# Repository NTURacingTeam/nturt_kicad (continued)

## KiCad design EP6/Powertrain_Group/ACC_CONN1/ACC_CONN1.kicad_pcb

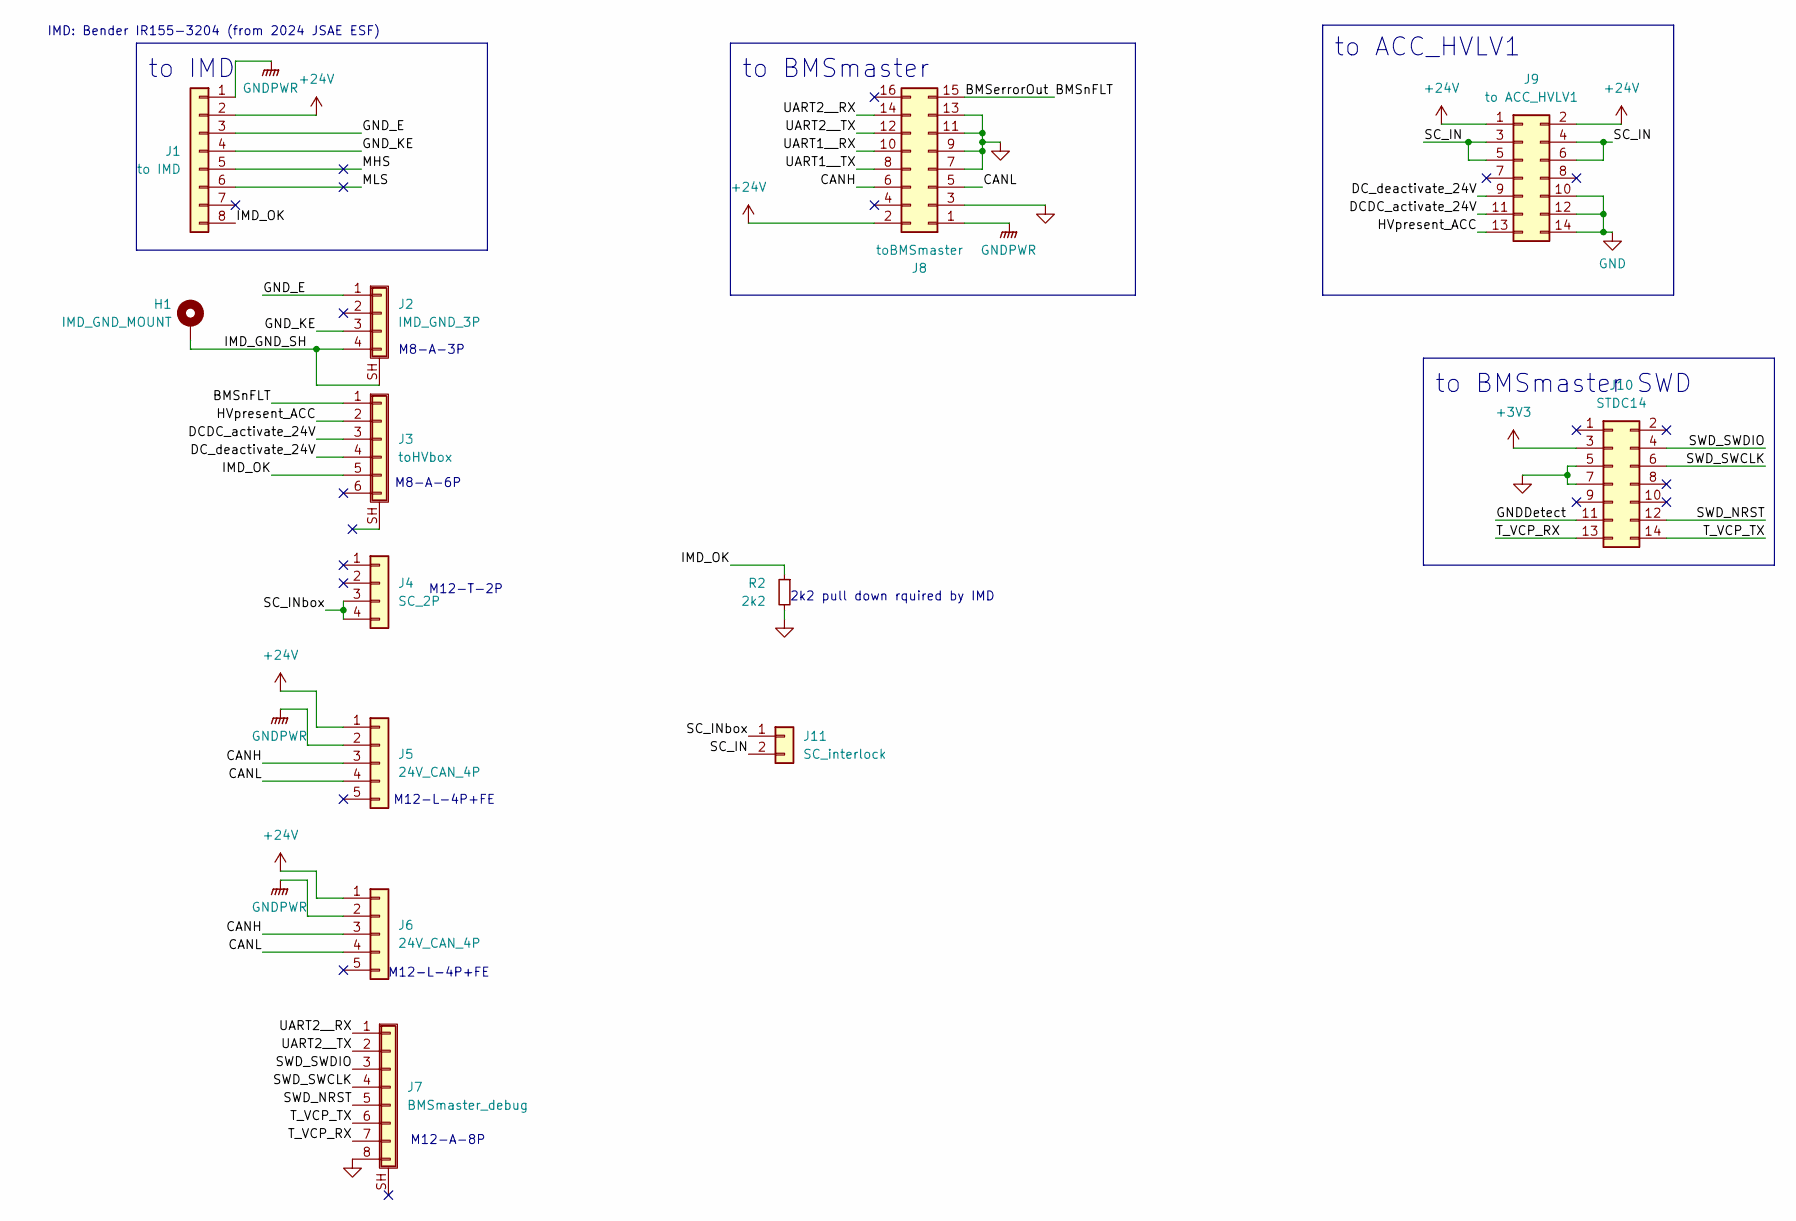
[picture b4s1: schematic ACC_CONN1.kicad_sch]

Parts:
H1: IMD_GND_MOUNT; MountingHole_3.2mm_M3_Pad_Via
J1: to IMD; JST_XH_B8B-XH-A_1x08_P2.50mm_Vertical
J2: IMD_GND_3P; WP-03F3-09-11
J3: toHVbox; WP-06F3-09-11
J4: SC_2P; NianYeong-M12-T-M4P
J5, J6: 24V_CAN_4P; NianYeong-M12-L-F5P
J7: BMSmaster_debug; NianYeong-M12-A-F8P-Shield
J8: toBMSmaster; IDC-Header_2x08_P2.54mm_Horizontal
J9: to ACC_HVLV1; IDC-Header_2x07_P2.54mm_Vertical
J10: STDC14; box_header_14P_pitch127
J11: SC_interlock; JST_VH_B2P-VH_1x02_P3.96mm_Vertical
R2: 2k2; R_0805_2012Metric

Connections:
+3V3: J10.3
+24V: J1.2, J5.1, J6.1, J8.2, J9.1, J9.2
/BMSerrorOut: J3.1, J8.15
/CANH: J5.3, J6.3, J8.6
/CANL: J5.4, J6.4, J8.5
/DCDC_activate_24V: J3.3, J9.11
/DC_deactivate_24V: J3.4, J9.9
/GNDDetect: J10.11
/GND_E: J1.3, J2.1
/GND_KE: J1.4, J2.3
/HVpresent_ACC: J3.2, J9.13
/IMD_GND_SH: H1.1, J2.4, J2.SH (Shield)
/IMD_OK: J1.8, J3.5, R2.1
/MHS: J1.5
/MLS: J1.6
/SC_IN: J9.3, J9.4, J9.5, J9.6, J11.2
/SC_INbox: J4.3, J4.4, J11.1
/SWD_NRST: J7.5, J10.12
/SWD_SWCLK: J7.4, J10.6
/SWD_SWDIO: J7.3, J10.4
/T_VCP_RX: J7.7, J10.13
/T_VCP_TX: J7.6, J10.14
/UART1__RX: J8.10
/UART1__TX: J8.8
/UART2__RX: J7.1, J8.14
/UART2__TX: J7.2, J8.12
GND: J7.8, J8.3, J8.7, J8.9, J8.11, J8.13, J9.10, J9.12, J9.14, J10.5, J10.7, R2.2
GNDPWR: J1.1, J5.2, J6.2, J8.1

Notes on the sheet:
M12-T-2P
to BMSmaster SWD
M12-L-4P+FE
to BMSmaster
to IMD
to ACC_HVLV1
M8-A-6P
M8-A-3P
2k2 pull down rquired by IMD
IMD: Bender IR155-3204 (from 2024 JSAE ESF)
M12-A-8P

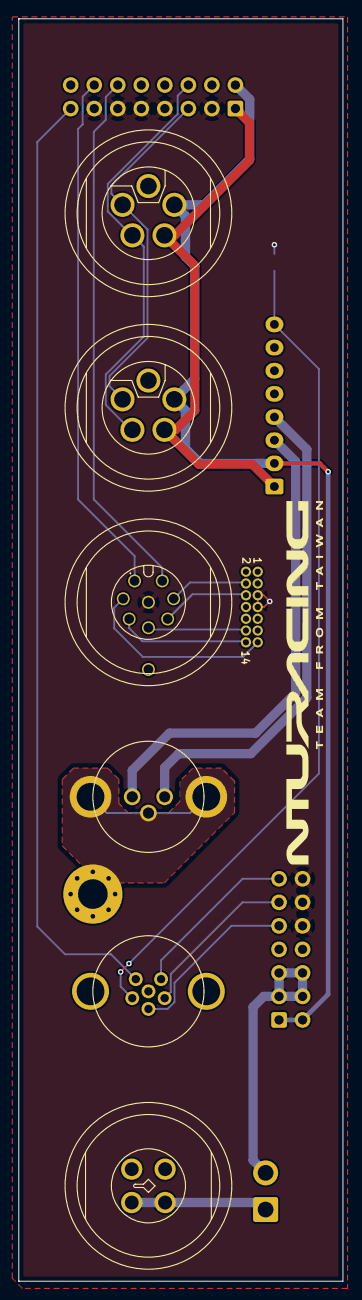
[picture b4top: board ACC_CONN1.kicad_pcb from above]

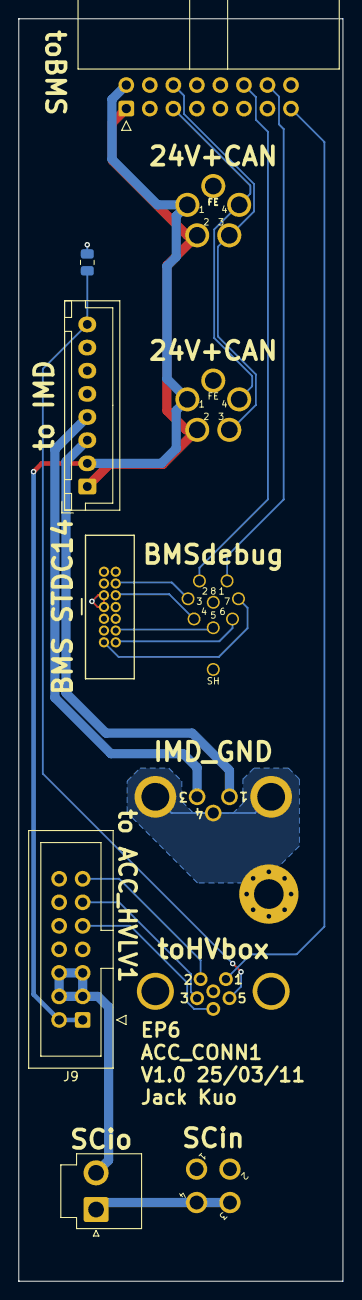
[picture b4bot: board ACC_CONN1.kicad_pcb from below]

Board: 2 copper layers, 35.0 x 136.3 mm, 13 parts (6 on the bottom side), 22 nets.

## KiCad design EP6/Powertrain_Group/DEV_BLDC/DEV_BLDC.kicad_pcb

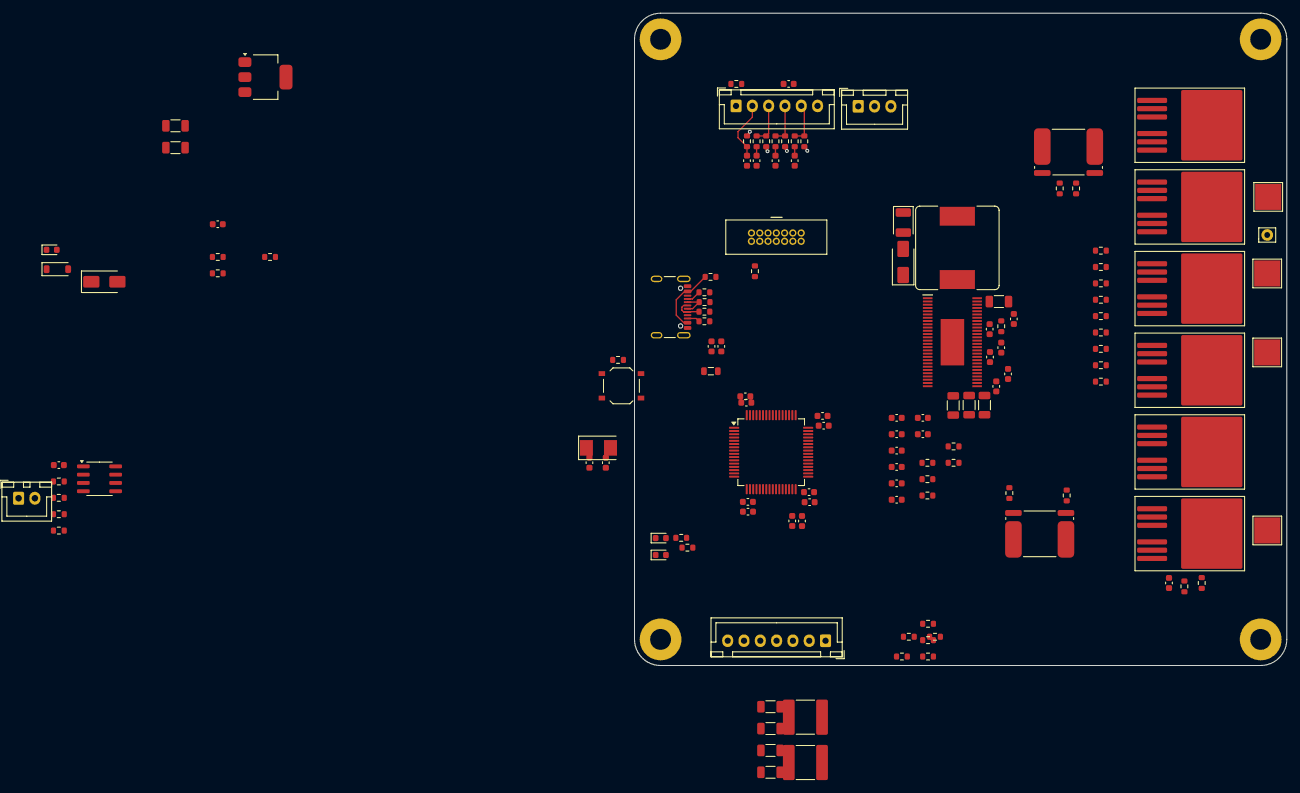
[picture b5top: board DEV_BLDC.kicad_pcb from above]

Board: 4 copper layers, 100.0 x 100.0 mm, 137 parts (0 on the bottom side), 92 nets.

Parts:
C1, C2: 33p; C_0603_1608Metric
C3, C4, C5, C6, C13: 10u 6V; C_0603_1608Metric
C7, C8, C9, C10, C14, C16: 0u1; C_0603_1608Metric
C11, C12, C21, C25, C26, C27, C28, C34: 2u2; C_0603_1608Metric
C15, C22, C39: 100n; C_0603_1608Metric
C17, C18, C19, C20: 4n7; C_0603_1608Metric
C23: 120p; C_0603_1608Metric
C24: 22n; C_0603_1608Metric
C29, C30, C36, C37, C47, C48, C49, C50: 10u 50V; C_1206_3216Metric
C31, C32: 47u 10V; C_1206_3216Metric
C33: 6n8; C_0603_1608Metric
C35, C38: 15u100V; C_2220_5750Metric
C40, C42, C43: 220n; C_0603_1608Metric
C44, C45: 2n2; C_0603_1608Metric
C46: 100u; CP_EIA-3528-12_Kemet-T
D1, D3: RED LED; LED_0603_1608Metric
D2: EMERALD LED; LED_0603_1608Metric
D4: 5.6V 1SMA5919A; D_SMA
D5: 3.3V 123 (BZT52B3V3); D_SOD-123
D7: SS54; D_SMA
FB1: GZ2012D601TF; L_0805_2012Metric
H1, H2, H3, H4: MountingHole_Pad; MountingHole_3.2mm_M3_Pad
IC1: DRV8302DCA; SOP50P810X120-57N
J1: STDC14; box_header_14P_pitch127
J2: USB_C_stm32; USB_C_Receptacle_GCT_USB4105-xx-A_16P_TopMnt_Horizontal
J3: CAN; JST_XH_B2B-XH-A_1x02_P2.50mm_Vertical
J4: HALL/Encoder; JST_XH_B6B-XH-A_1x06_P2.50mm_Vertical
J5: PWR_COMM; JST_XH_B7B-XH-A_1x07_P2.50mm_Vertical
J6: SERVER; JST_XH_B3B-XH-A_1x03_P2.50mm_Vertical
L2: 22uH ?A (); L_Bourns_SRR1260
Q1, Q2, Q3, Q4, Q5, Q6: IRFS7530-7P; TO-263-6
R1, R39, R40, R41, R42: 100R; R_0603_1608Metric
R2, R18, R23, R27: 10k; R_0603_1608Metric
R4, R30, R35, R37, R43, R49, R52: 39k; R_0603_1608Metric
R5, R15, R16, R17, R19, R20, R21, R31, R36, R38: 2k2; R_0603_1608Metric
R6, R7: 5k1; R_0603_1608Metric
R8, R9, R26: 10R; R_0603_1608Metric
R10, R12, R13, R14: 0R; R_0603_1608Metric
R11: 120R; R_0603_1608Metric
R22: NTC10k; R_0603_1608Metric
R24, R25, R32: 1k; R_0603_1608Metric
R28: 18k; R_0603_1608Metric
R29: 220k; R_0603_1608Metric
R33: 15k; R_0603_1608Metric
R34: 3k3; R_0603_1608Metric
R44: 1M; R_0603_1608Metric
R45, R46, R47, R48, R50, R51: 4R7; R_0603_1608Metric
R53, R54: SHUNT; R_Shunt_Isabellenhuette_BVR4026
SW1: TS-1187A-B-A-B; SW_Push_1P1T_XKB_TS-1187A
TP1: power+; Pin_D0.9mm_L10.0mm_W2.4mm_FlatFork
TP2: power-; TestPoint_Pad_4.0x4.0mm
TP3: P1; TestPoint_Pad_4.0x4.0mm
TP4: P2; TestPoint_Pad_4.0x4.0mm
TP5: P3; TestPoint_Pad_4.0x4.0mm
U1: STM32F405RGT6; LQFP-64_10x10mm_P0.5mm
U2: TJA1051T-3; SOIC-8_3.9x4.9mm_P1.27mm
U3: AMS1117-3.3; SOT-223-3_TabPin2
Y1: 8MHz X50328MSB2GI; Crystal_SMD_5032-2Pin_5.0x3.2mm

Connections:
+3V3: C3.1, C4.1, C5.1, C6.1, C7.1, C8.1, C9.1, C10.1, C16.1, C32.1, D5.1 (K), FB1.1, IC1.9 (M_OC), IC1.24 (REF), J1.3, J5.6, R15.1, R16.1, R17.1, R18.1, R22.1, R32.1, U1.1 (VBAT), U1.19 (VDD), U1.32 (VDD), U1.48 (VDD), U1.64 (VDD), U2.5 (VIO), U3.2 (VO)
+5V: C31.1, C46.1, D4.1 (K), J4.6, J5.7, J6.2, L2.2, R10.1, R28.1, U2.3 (VCC), U3.3 (VI)
/CAN/CANH: J3.2, R11.1, U2.7 (CANH)
/CAN/CANL: J3.1, R11.2, U2.6 (CANL)
/CAN/CAN_RX: R14.2, U1.61 (PB8)
/CAN/CAN_TX: R13.2, U1.62 (PB9)
/Filters/HALL1_IN: J4.5, R17.2, R21.1
/Filters/HALL1_OUT: C20.1, R21.2, U1.52 (PC11)
/Filters/HALL2_IN: J4.4, R16.2, R20.1
/Filters/HALL2_OUT: C19.1, R20.2, U1.59 (PB7)
/Filters/HALL3_IN: J4.3, R15.2, R19.1
/Filters/HALL3_OUT: C18.1, R19.2, U1.58 (PB6)
/Filters/TEMP_IN: C17.1, J4.2, R18.2, U1.8 (PC0)
/MCU/3V3_REF: C13.1, C14.1, FB1.2, U1.13 (VDDA)
/MCU/ADC_TEMP: C21.1, R22.2, R23.1, U1.17 (PA3)
/MCU/AN_IN: C15.1, R4.2, R5.1, U1.10 (PC2)
/MCU/BR_SO1: IC1.25 (SO1), U1.27 (PB1)
/MCU/BR_SO2: IC1.26 (SO2), U1.26 (PB0)
/MCU/DC_CAL: IC1.12 (DC_CAL), U1.33 (PB12)
/MCU/EN_GATE: IC1.16 (EN_GATE), U1.51 (PC10)
/MCU/FAULT: IC1.6 (NFAULT), U1.53 (PC12)
/MCU/H1: IC1.17 (INH_A), U1.43 (PA10)
/MCU/H2: IC1.19 (INH_B), U1.42 (PA9)
/MCU/H3: IC1.21 (INH_C), U1.41 (PA8)
/MCU/L1: IC1.18 (INL_A), U1.36 (PB15)
/MCU/L2: IC1.20 (INL_B), U1.35 (PB14)
/MCU/L3: IC1.22 (INL_C), U1.34 (PB13)
/MCU/LED_GREEN: R25.1, U1.24 (PC4)
/MCU/LED_RED: R24.1, U1.25 (PC5)
/MCU/MISO_ADC_EXT2: J5.2, U1.22 (PA6)
/MCU/NRST: J1.12, R1.2, U1.7 (NRST)
/MCU/OSC_IN: C1.1, U1.5 (PH0), Y1.1
/MCU/OSC_OUT: C2.1, U1.6 (PH1), Y1.2
/MCU/RESET: R1.1, SW1.2
/MCU/RX_SCL_MOSI: J5.3, U1.23 (PA7), U1.29 (PB10), U1.38 (PC7)
/MCU/SCK_ADC_EXT: J5.5, U1.21 (PA5)
/MCU/SENS1: R30.2, R31.1, U1.16 (PA2)
/MCU/SENS2: R35.2, R36.1, U1.15 (PA1)
/MCU/SENS3: R37.2, R38.1, U1.14 (PA0)
/MCU/SERVO: C22.1, R26.2, U1.57 (PB5)
/MCU/SWCLK: J1.6, U1.49 (PA14)
/MCU/SWDIO: J1.4, U1.46 (PA13)
/MCU/TX_SDA_NSS: J5.4, U1.20 (PA4), U1.30 (PB11), U1.37 (PC6)
/MCU/USB_DM: R8.1, U1.44 (PA11)
/MCU/USB_DP: R9.1, U1.45 (PA12)
/MOSFETdriver/H1_LOW: IC1.44 (SL_A), Q2.2 (S), Q2.3 (S), Q2.5 (S), Q2.6 (S), Q2.7 (S), R43.2, R54.1
/MOSFETdriver/H1_VS: C40.2, IC1.46 (SH_A), Q1.2 (S), Q1.3 (S), Q1.5 (S), Q1.6 (S), Q1.7 (S), Q2.4 (D), R37.1, TP3.1
/MOSFETdriver/H2_VS: C42.2, IC1.41 (SH_B), Q3.2 (S), Q4.4 (D), R35.1, TP4.1
/MOSFETdriver/H3_LOW: IC1.34 (SL_C), Q6.2 (S), Q6.3 (S), Q6.5 (S), Q6.6 (S), Q6.7 (S), R52.2, R53.1
/MOSFETdriver/H3_VS: C43.2, IC1.36 (SH_C), Q5.2 (S), Q6.4 (D), R30.1, TP5.1
/MOSFETdriver/M_H1: IC1.47 (GH_A), R45.1
/MOSFETdriver/M_H2: IC1.42 (GH_B), R47.1
/MOSFETdriver/M_H3: IC1.37 (GH_C), R50.1
/MOSFETdriver/M_L1: IC1.45 (GL_A), R46.1
/MOSFETdriver/M_L2: IC1.40 (GL_B), R48.1
/MOSFETdriver/M_L3: IC1.35 (GL_C), R51.1
/MOSFETdriver/SH1_A: R39.2, R53.2
/MOSFETdriver/SH1_B: R40.2, R53.3
/MOSFETdriver/SH2_A: R41.2, R54.2
/MOSFETdriver/SH2_B: R42.2, R54.3
/USB_D+: J2.A6 (D+), J2.B6 (D+), R9.2
/USB_D-: J2.A7 (D-), J2.B7 (D-), R8.2
GND: C1.2, C2.2, C3.2, C4.2, C5.2, C6.2, C7.2, C8.2, C9.2, C10.2, C11.2, C12.2, C13.2, C14.2, C15.2, C16.2, C17.2, C18.2, C19.2, C20.2, C21.2, C22.2, C23.2, C25.1, C26.1, C27.1, C28.1, C29.2, C30.2, C31.2, C32.2, C34.1, C35.2, C36.2, C37.2, C38.2, C46.2, C47.2, C48.2, C49.2, C50.2, D1.1 (K), D2.1 (K), D3.1 (K), D4.2 (A), D5.2 (A), D7.2 (A), IC1.8 (M_PWM), IC1.10 (GAIN), IC1.28 (AGND), IC1.39 (SL_B), IC1.57 (GND), J1.5, J1.7, J2.A1 (GND), J2.A12 (GND), J2.B1 (GND), J2.B12 (GND), J4.1, J5.1, J6.3, Q4.2 (S), Q4.3 (S), Q4.5 (S), Q4.6 (S), Q4.7 (S), R2.2, R5.2, R6.1, R7.1, R12.2, R23.2, R27.1, R29.2, R31.2, R33.2, R34.2, R36.2, R38.2, R44.2, R49.2, R53.4, R54.4, SW1.1, TP2.1, U1.12 (VSSA), U1.18 (VSS), U1.63 (VSS), U2.2 (GND), U3.1 (GND)
unnamed: C25.2, C26.2, IC1.13 (GVDD)
unnamed: C27.2, C34.2, IC1.11 (OC_ADJ), IC1.23 (DVDD)
unnamed: C39.2, D7.1 (K), IC1.50 (PH_1), IC1.51 (PH_2), L2.1
unnamed: C44.1, IC1.33 (SN1), R39.1
unnamed: C44.2, IC1.32 (SP1), R40.1
unnamed: C45.1, IC1.31 (SN2), R41.1
unnamed: C45.2, IC1.30 (SP2), R42.1
unnamed: D1.2 (A), R24.2
unnamed: D2.2 (A), R25.2
unnamed: D3.2 (A), R32.2
unnamed: J2.A5 (CC1), R6.2
unnamed: J2.B5 (CC2), R7.2
unnamed: J2.A4 (VBUS), J2.A9 (VBUS), J2.B4 (VBUS), J2.B9 (VBUS), R10.2
unnamed: J6.1, R26.1
unnamed: Q1.1 (G), R45.2
unnamed: Q2.1 (G), R43.1, R46.2
unnamed: Q3.1 (G), R47.2
unnamed: Q4.1 (G), R48.2, R49.1
unnamed: Q5.1 (G), R50.2
unnamed: Q6.1 (G), R51.2, R52.1
unnamed: IC1.3 (VSENSE), R28.2, R34.1
unnamed: R2.1, U1.60 (BOOT0)
unnamed: C11.1, U1.31 (VCAP_1)
unnamed: C12.1, U1.47 (VCAP_2)
unnamed: R14.1, U2.4 (RXD)
unnamed: R12.1, U2.8 (S)
unnamed: R13.1, U2.1 (TXD)
V_SUPPLY: C47.1, C48.1, C49.1, C50.1, IC1.29 (PVDD1), IC1.53 (PVDD2_1), IC1.54 (PVDD2_2)
Vsupply: C29.1, C30.1, C35.1, C36.1, C37.1, C38.1, Q1.4 (D), Q3.4 (D), Q5.4 (D), R4.1, TP1.1
